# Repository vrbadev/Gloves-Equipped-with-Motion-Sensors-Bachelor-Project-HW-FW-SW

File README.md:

# Gloves Equipped with Motion Sensors (HW & FW & SW)
 This project was created as a part of my bachelor thesis at the Czech Technical University. It contains complete hardware, firmware and software designs for smart Bluetooth gloves equipped with 15 6-DOF IMU sensors.

## About the Bachelor Thesis (Abstract)

This bachelor thesis focuses on the development of gloves equipped with motion sensors. The result of this work is supposed to be a functional device including 3D visualisation of measured bending of all fingers, so hand gestures can be determined. First of all, the theory of Bluetooth Low Energy devices is presented.The next chapter contains an explanation of hardware design details. Then the software implementation for the programmable BLE module is presented. Explanation of the theory of quaternion representation of the rotation and orientation in space for Madgwick's AHRS algorithm can be also found in this work. Python language has been chosen for implementing the visualisation. The thesis is completed with achieved results and ideas for further development.

Full text (in Czech language) is available at: https://dspace.cvut.cz/handle/10467/87657?locale-attribute=en

## Repository Contents

* **Hardware folder** - Contains complete Autodesk EAGLE projects for all related PCBs, including PDF schematics and layout visualisations.
* **Gerber folder** - Contains GERBER production archives for all of the designed PCBs.
* **Firmware folder** - Contains complete Keil uVision project with the firmware for the STMicroelectronics BlueNRG-M2SA Bluetooth module.
* **Software folder** - Contains Python software used for processing of the IMU data and for the visualisation.

## 3D Visualisation Software

A screenshot of the Python visualiser and the static code analysis are shown below.

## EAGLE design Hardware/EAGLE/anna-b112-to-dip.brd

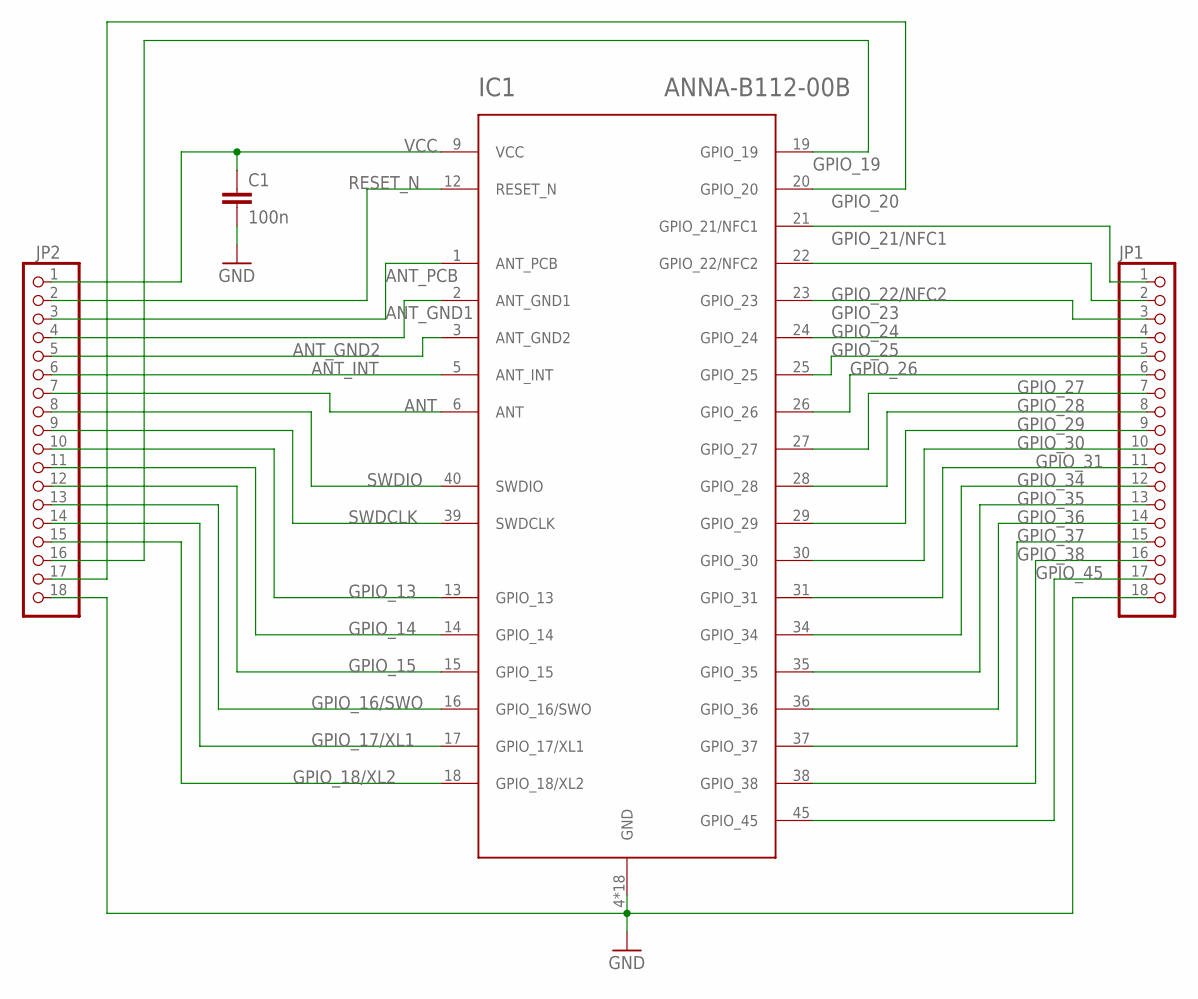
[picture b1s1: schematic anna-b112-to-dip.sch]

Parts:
C1: 100n; C0805
IC1: ANNA-B112-00B; ANNA-B112
JP1, JP2: PINHD-1X18; 1X18

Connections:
ANT: IC1.6 (ANT), JP2.7
ANT_GND1: IC1.2 (ANT_GND1), JP2.4
ANT_GND2: IC1.3 (ANT_GND2), JP2.5
ANT_INT: IC1.5 (ANT_INT), JP2.6
ANT_PCB: IC1.1 (ANT_PCB), JP2.3
GND: C1.2, IC1.4 (GND), IC1.7 (GND), IC1.8 (GND), IC1.10 (GND), IC1.11 (GND), IC1.32 (GND), IC1.33 (GND), IC1.41 (GND), IC1.42 (GND), IC1.43 (GND), IC1.44 (GND), IC1.46 (GND), IC1.47 (GND), IC1.48 (GND), IC1.49 (GND), IC1.50 (GND), IC1.51 (GND), IC1.52 (GND), JP1.18, JP2.18
GPIO_13: IC1.13 (GPIO_13), JP2.10
GPIO_14: IC1.14 (GPIO_14), JP2.11
GPIO_15: IC1.15 (GPIO_15), JP2.12
GPIO_16/SWO: IC1.16 (GPIO_16/SWO), JP2.13
GPIO_17/XL1: IC1.17 (GPIO_17/XL1), JP2.14
GPIO_18/XL2: IC1.18 (GPIO_18/XL2), JP2.15
GPIO_19: IC1.19 (GPIO_19), JP2.16
GPIO_20: IC1.20 (GPIO_20), JP2.17
GPIO_21/NFC1: IC1.21 (GPIO_21/NFC1), JP1.1
GPIO_22/NFC2: IC1.22 (GPIO_22/NFC2), JP1.2
GPIO_23: IC1.23 (GPIO_23), JP1.3
GPIO_24: IC1.24 (GPIO_24), JP1.4
GPIO_25: IC1.25 (GPIO_25), JP1.5
GPIO_26: IC1.26 (GPIO_26), JP1.6
GPIO_27: IC1.27 (GPIO_27), JP1.7
GPIO_28: IC1.28 (GPIO_28), JP1.8
GPIO_29: IC1.29 (GPIO_29), JP1.9
GPIO_30: IC1.30 (GPIO_30), JP1.10
GPIO_31: IC1.31 (GPIO_31), JP1.11
GPIO_34: IC1.34 (GPIO_34), JP1.12
GPIO_35: IC1.35 (GPIO_35), JP1.13
GPIO_36: IC1.36 (GPIO_36), JP1.14
GPIO_37: IC1.37 (GPIO_37), JP1.15
GPIO_38: IC1.38 (GPIO_38), JP1.16
GPIO_45: IC1.45 (GPIO_45), JP1.17
RESET_N: IC1.12 (RESET_N), JP2.2
SWDCLK: IC1.39 (SWDCLK), JP2.9
SWDIO: IC1.40 (SWDIO), JP2.8
VCC: C1.1, IC1.9 (VCC), JP2.1

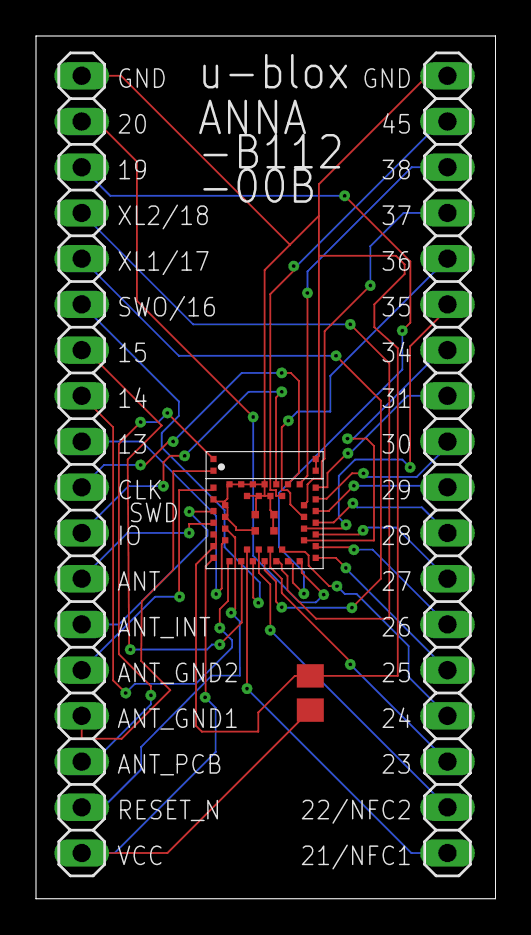
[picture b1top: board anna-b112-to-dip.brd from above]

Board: 2 copper layers, 25.5 x 47.9 mm, 4 parts (0 on the bottom side), 35 nets.

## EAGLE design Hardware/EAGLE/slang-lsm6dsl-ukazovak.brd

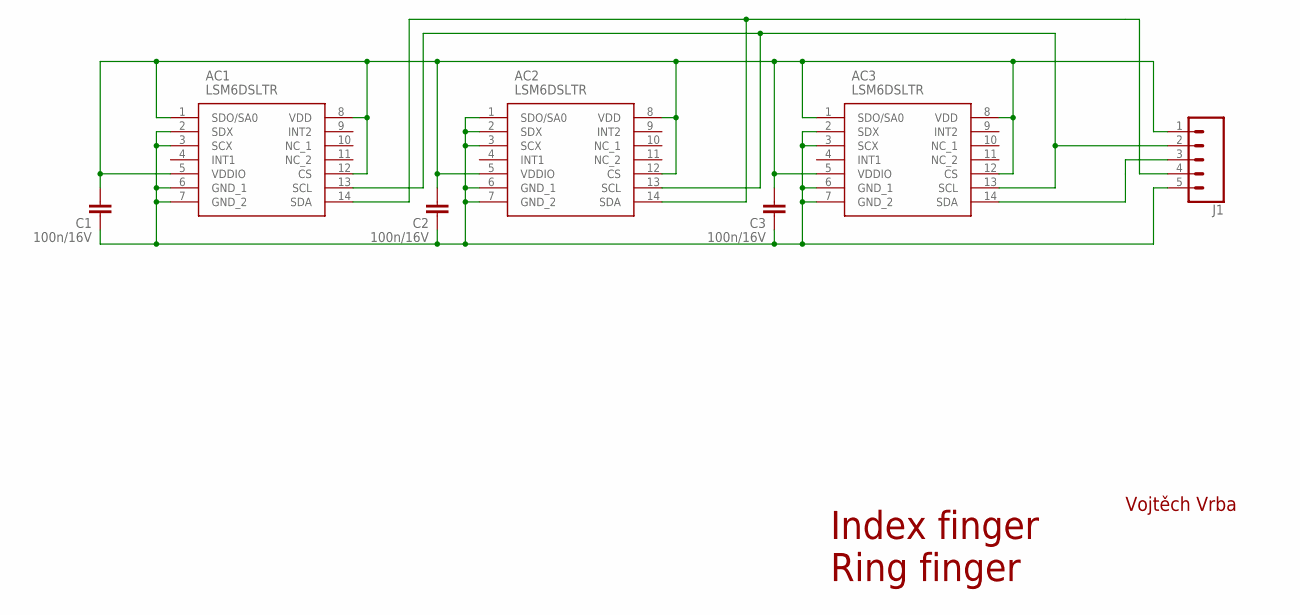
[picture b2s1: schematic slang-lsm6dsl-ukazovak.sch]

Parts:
AC1, AC2, AC3: LSM6DSLTR; LGA-14(2.5X3X0.86)
C1, C2, C3: 100n/16V; C0603
J1: CONN_051.27MM; 1X05_1.27MM

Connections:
GND: AC1.2 (SDX), AC1.3 (SCX), AC1.6 (GND_1), AC1.7 (GND_2), AC2.1 (SDO/SA0), AC2.2 (SDX), AC2.3 (SCX), AC2.6 (GND_1), AC2.7 (GND_2), AC3.2 (SDX), AC3.3 (SCX), AC3.6 (GND_1), AC3.7 (GND_2), C1.1, C2.1, C3.1, J1.5
SCL: AC1.13 (SCL), AC2.13 (SCL), AC3.13 (SCL), J1.2
SDA: AC1.14 (SDA), AC2.14 (SDA), J1.4
SDA2: AC3.14 (SDA), J1.3
VDD: AC1.1 (SDO/SA0), AC1.5 (VDDIO), AC1.8 (VDD), AC1.12 (CS), AC2.5 (VDDIO), AC2.8 (VDD), AC2.12 (CS), AC3.1 (SDO/SA0), AC3.5 (VDDIO), AC3.8 (VDD), AC3.12 (CS), C1.2, C2.2, C3.2, J1.1

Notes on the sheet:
Index finger Ring finger
Vojtěch Vrba

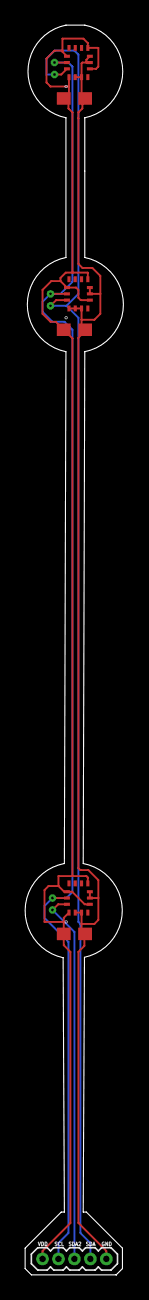
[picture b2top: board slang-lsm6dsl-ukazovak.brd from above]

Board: 2 copper layers, 7.8 x 99.5 mm, 7 parts (0 on the bottom side), 5 nets.

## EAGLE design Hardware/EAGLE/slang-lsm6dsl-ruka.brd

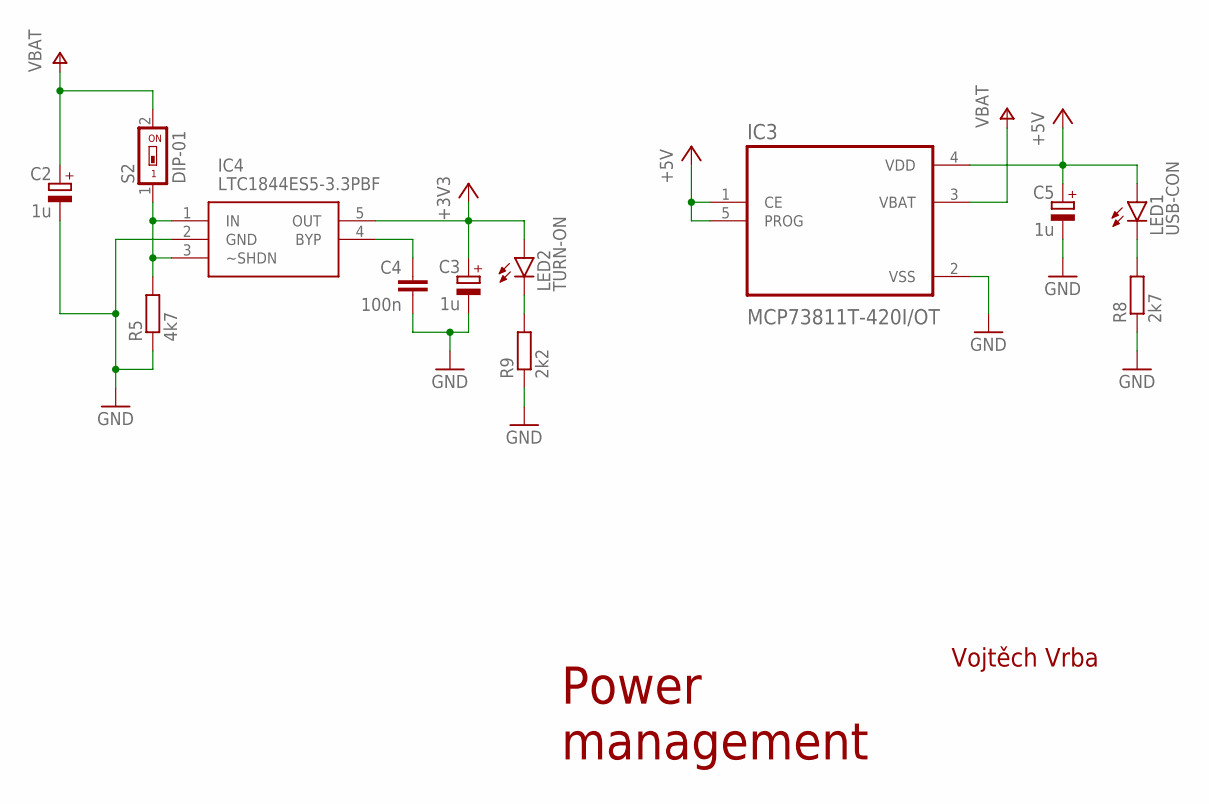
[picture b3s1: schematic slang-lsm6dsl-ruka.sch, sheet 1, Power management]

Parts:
C2, C3, C5: 1u; SMC_A
C4: 100n; C0805
IC3: MCP73811T-420I/OT; SOT95P280X145-5N
IC4: LTC1844ES5-3.3PBF; SOT95P280X100-5N
LED1: USB-CON; CHIP-LED0805
LED2: TURN-ON; CHIP-LED0805
R5: 4k7; R0805
R8: 2k7; R0805
R9: 2k2; R0805
S2: DIP-01; SMS-001

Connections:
+3V3: C3.+, IC4.5 (OUT), LED2.A; also elsewhere on the board
+5V: C5.+, IC3.1 (CE), IC3.4 (VDD), IC3.5 (PROG), LED1.A; also elsewhere on the board
GND: C2.-, C3.-, C4.2, C5.-, IC3.2 (VSS), IC4.2 (GND), R5.1, R8.1, R9.1; also elsewhere on the board
unnamed: LED1.C, R8.2
unnamed: C4.1, IC4.4 (BYP)
unnamed: IC4.1 (IN), IC4.3 (~SHDN), R5.2, S2.1
unnamed: LED2.C, R9.2
V+: C2.+, IC3.3 (VBAT), S2.2; also elsewhere on the board

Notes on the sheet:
Vojtěch Vrba
Power management

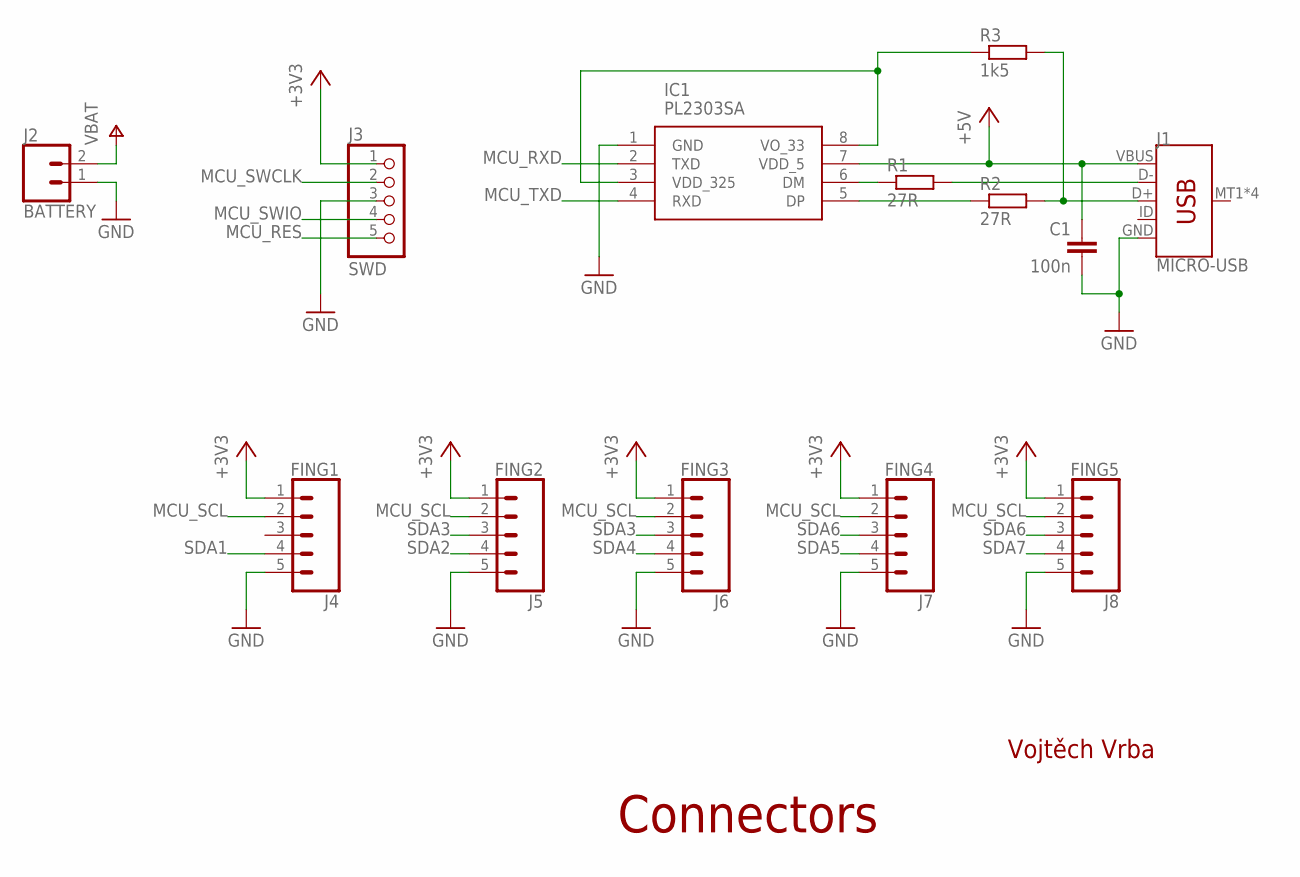
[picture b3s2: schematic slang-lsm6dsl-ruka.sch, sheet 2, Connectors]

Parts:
C1: 100n; C0805
IC1: PL2303SA; SOIC127P600X170-8N
J1: MICRO-USB; USB-MICROB
J2: BATTERY; SCREWTERMINAL-5MM-2
J3: SWD; 1X05/90
J4: FING1; 1X05_1.27MM
J5: FING2; 1X05_1.27MM
J6: FING3; 1X05_1.27MM
J7: FING4; 1X05_1.27MM
J8: FING5; 1X05_1.27MM
R1, R2: 27R; R0805
R3: 1k5; R0805

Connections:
+3V3: J3.1, J4.1, J5.1, J6.1, J7.1, J8.1; also elsewhere on the board
+5V: C1.1, IC1.7 (VDD_5), J1.VBUS; also elsewhere on the board
GND: C1.2, IC1.1 (GND), J1.GND, J2.1, J3.3, J4.5, J5.5, J6.5, J7.5, J8.5; also elsewhere on the board
MCU_RES: J3.5; also elsewhere on the board
MCU_RXD: IC1.2 (TXD); also elsewhere on the board
MCU_SCL: J4.2, J5.2, J6.2, J7.2, J8.2; also elsewhere on the board
MCU_SWCLK: J3.2; also elsewhere on the board
MCU_SWIO: J3.4; also elsewhere on the board
MCU_TXD: IC1.4 (RXD); also elsewhere on the board
unnamed: IC1.6 (DM), R1.1
unnamed: J1.D-, R1.2
unnamed: J1.D+, R2.2, R3.2
unnamed: IC1.5 (DP), R2.1
unnamed: IC1.3 (VDD_325), IC1.8 (VO_33), R3.1
SDA1: J4.4; also elsewhere on the board
SDA2: J5.4; also elsewhere on the board
SDA3: J5.3, J6.3; also elsewhere on the board
SDA4: J6.4; also elsewhere on the board
SDA5: J7.4; also elsewhere on the board
SDA6: J7.3, J8.3; also elsewhere on the board
SDA7: J8.4; also elsewhere on the board
V+: J2.2; also elsewhere on the board

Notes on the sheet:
Connectors
Vojtěch Vrba

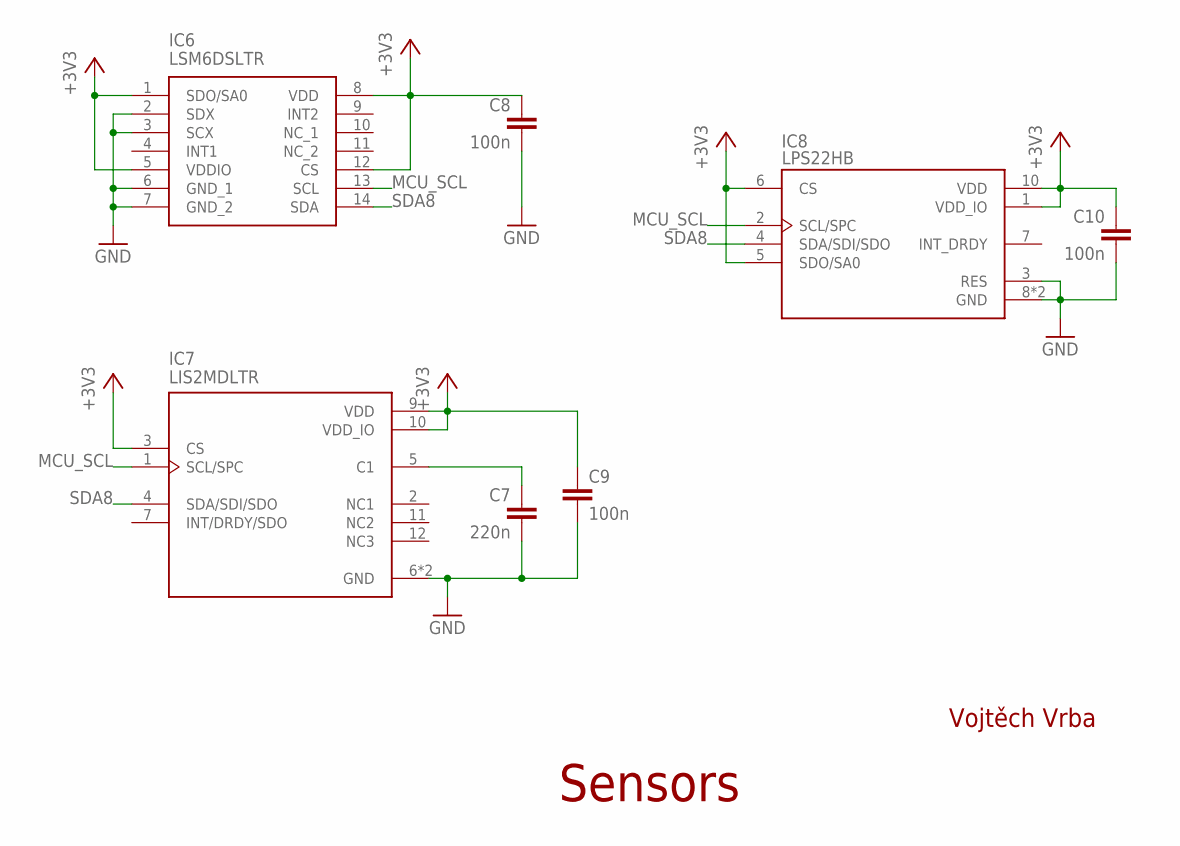
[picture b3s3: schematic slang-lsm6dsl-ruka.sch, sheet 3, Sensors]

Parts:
C7: 220n; C0805
C8, C9, C10: 100n; C0805
IC6: LSM6DSLTR; LGA-14(2.5X3X0.86)
IC7: LIS2MDLTR; PQFN50P200X200X70-12N
IC8: LPS22HB; LGA10R50P2X3_200X200X80

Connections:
+3V3: C8.1, C9.1, C10.1, IC6.1 (SDO/SA0), IC6.5 (VDDIO), IC6.8 (VDD), IC6.12 (CS), IC7.3 (CS), IC7.9 (VDD), IC7.10 (VDD_IO), IC8.1 (VDD_IO), IC8.5 (SDO/SA0), IC8.6 (CS), IC8.10 (VDD); also elsewhere on the board
GND: C7.2, C8.2, C9.2, C10.2, IC6.2 (SDX), IC6.3 (SCX), IC6.6 (GND_1), IC6.7 (GND_2), IC7.6 (GND), IC7.8 (GND), IC8.3 (RES), IC8.8 (GND), IC8.9 (GND); also elsewhere on the board
MCU_SCL: IC6.13 (SCL), IC7.1 (SCL/SPC), IC8.2 (SCL/SPC); also elsewhere on the board
unnamed: C7.1, IC7.5 (C1)
SDA8: IC6.14 (SDA), IC7.4 (SDA/SDI/SDO), IC8.4 (SDA/SDI/SDO); also elsewhere on the board

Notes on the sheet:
Vojtěch Vrba
Sensors

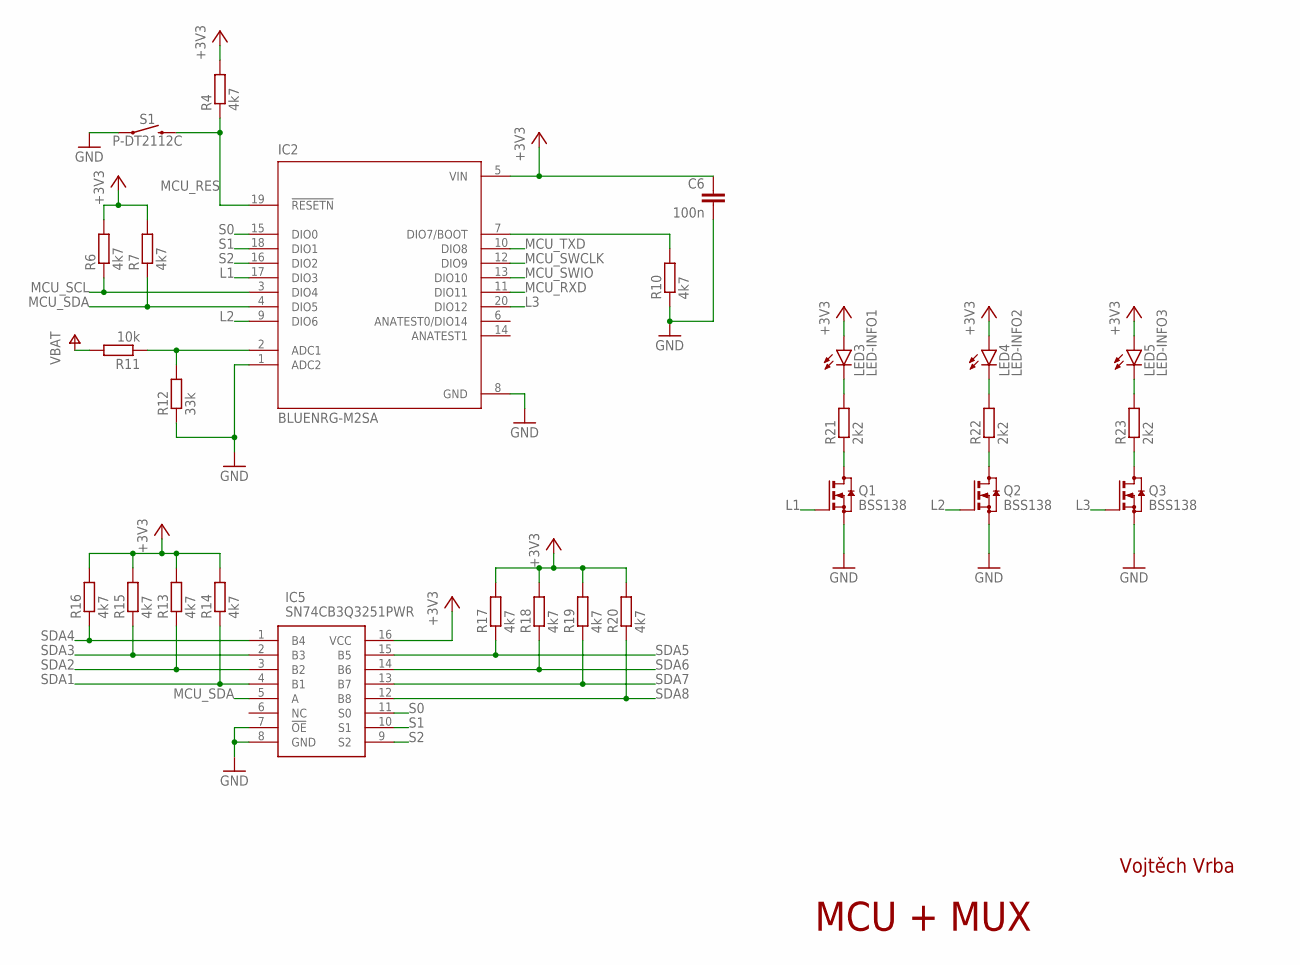
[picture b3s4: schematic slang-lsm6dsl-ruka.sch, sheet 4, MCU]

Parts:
C6: 100n; C0805
IC2: BLUENRG-M2SA; XCVR_BLUENRG-M2SA
IC5: SN74CB3Q3251PWR; SOP65P640X120-16N
LED3: LED-INFO1; CHIP-LED0805
LED4: LED-INFO2; CHIP-LED0805
LED5: LED-INFO3; CHIP-LED0805
Q1, Q2, Q3: BSS138; SOT23
R4, R6, R7, R10, R13, R14, R15, R16, R17, R18, R19, R20: 4k7; R0805
R11: 10k; R0805
R12: 33k; R0805
R21, R22, R23: 2k2; R0805
S1: P-DT2112C; TACTILE_SWITCH_SMD_6.0X3.5MM

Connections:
+3V3: C6.1, IC2.5 (VIN), IC5.16 (VCC), LED3.A, LED4.A, LED5.A, R4.2, R6.2, R7.2, R13.2, R14.2, R15.2, R16.2, R17.2, R18.2, R19.2, R20.2; also elsewhere on the board
GND: C6.2, IC2.1 (ADC2), IC2.8 (GND), IC5.7 (!OE), IC5.8 (GND), Q1.2 (S), Q2.2 (S), Q3.2 (S), R10.1, R12.1, S1.1; also elsewhere on the board
L1: IC2.17 (DIO3), Q1.1 (G)
L2: IC2.9 (DIO6), Q2.1 (G)
L3: IC2.20 (DIO12), Q3.1 (G)
MCU_RES: IC2.19 (!RESETN), R4.1, S1.2; also elsewhere on the board
MCU_RXD: IC2.11 (DIO11); also elsewhere on the board
MCU_SCL: IC2.3 (DIO4), R6.1; also elsewhere on the board
MCU_SDA: IC2.4 (DIO5), IC5.5 (A), R7.1
MCU_SWCLK: IC2.12 (DIO9); also elsewhere on the board
MCU_SWIO: IC2.13 (DIO10); also elsewhere on the board
MCU_TXD: IC2.10 (DIO8); also elsewhere on the board
unnamed: IC2.7 (DIO7/BOOT), R10.2
unnamed: IC2.2 (ADC1), R11.1, R12.2
unnamed: LED3.C, R21.2
unnamed: Q1.3 (D), R21.1
unnamed: LED4.C, R22.2
unnamed: Q2.3 (D), R22.1
unnamed: LED5.C, R23.2
unnamed: Q3.3 (D), R23.1
S0: IC2.15 (DIO0), IC5.11 (S0)
S1: IC2.18 (DIO1), IC5.10 (S1)
S2: IC2.16 (DIO2), IC5.9 (S2)
SDA1: IC5.4 (B1), R14.1; also elsewhere on the board
SDA2: IC5.3 (B2), R13.1; also elsewhere on the board
SDA3: IC5.2 (B3), R15.1; also elsewhere on the board
SDA4: IC5.1 (B4), R16.1; also elsewhere on the board
SDA5: IC5.15 (B5), R17.1; also elsewhere on the board
SDA6: IC5.14 (B6), R18.1; also elsewhere on the board
SDA7: IC5.13 (B7), R19.1; also elsewhere on the board
SDA8: IC5.12 (B8), R20.1; also elsewhere on the board
V+: R11.2; also elsewhere on the board

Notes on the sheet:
Vojtěch Vrba
MCU + MUX

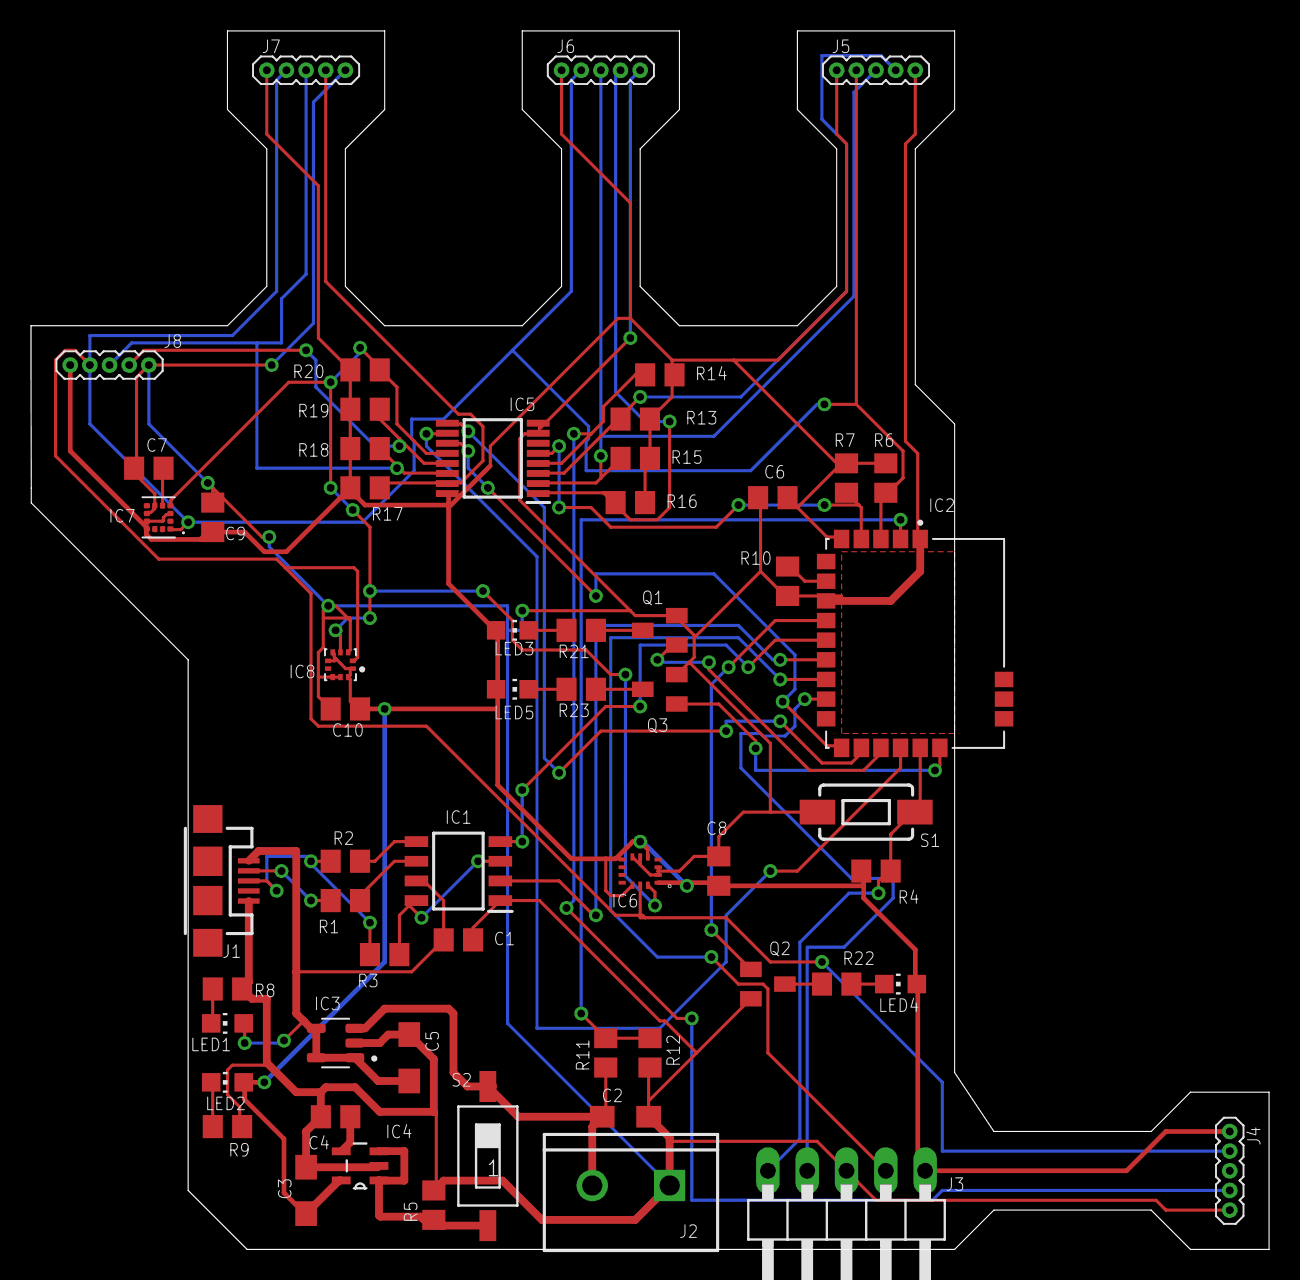
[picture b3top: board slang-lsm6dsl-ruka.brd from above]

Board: 2 copper layers, 80.0 x 78.7 mm, 59 parts (0 on the bottom side), 43 nets.

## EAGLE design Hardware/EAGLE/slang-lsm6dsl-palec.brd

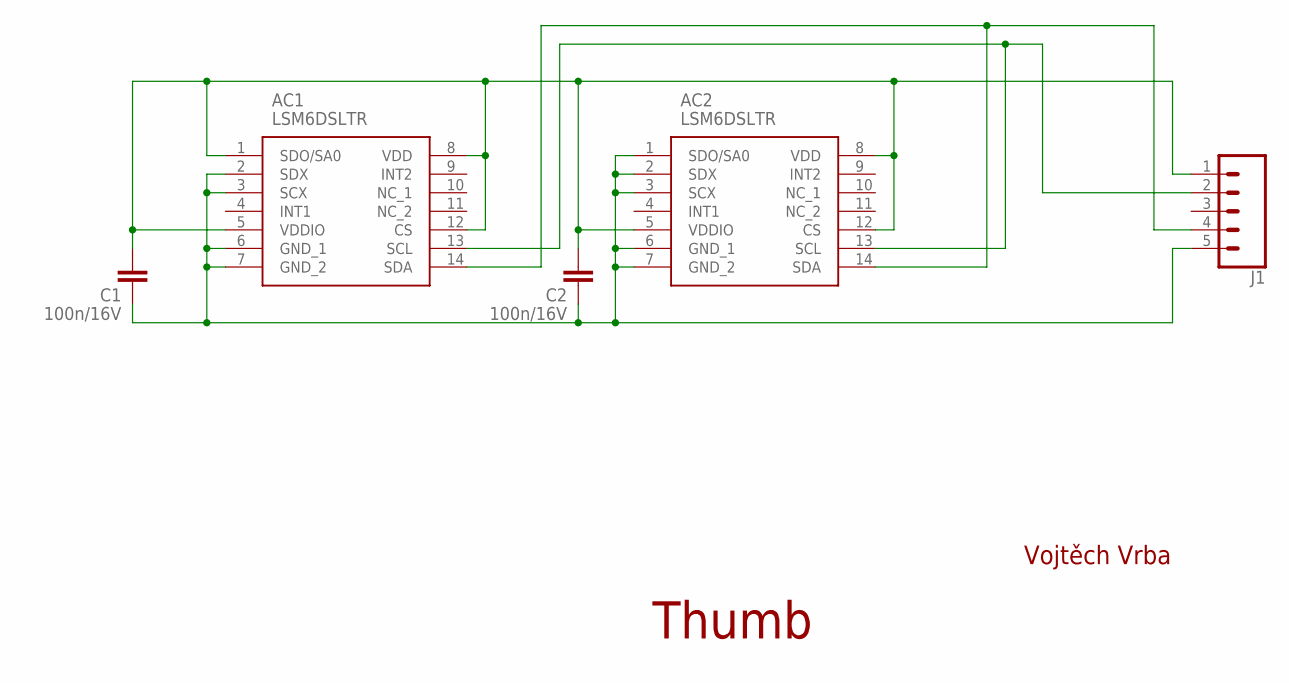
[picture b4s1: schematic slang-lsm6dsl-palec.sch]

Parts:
AC1, AC2: LSM6DSLTR; LGA-14(2.5X3X0.86)
C1, C2: 100n/16V; C0603
J1: CONN_051.27MM; 1X05_1.27MM

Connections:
GND: AC1.2 (SDX), AC1.3 (SCX), AC1.6 (GND_1), AC1.7 (GND_2), AC2.1 (SDO/SA0), AC2.2 (SDX), AC2.3 (SCX), AC2.6 (GND_1), AC2.7 (GND_2), C1.1, C2.1, J1.5
SCL: AC1.13 (SCL), AC2.13 (SCL), J1.2
SDA: AC1.14 (SDA), AC2.14 (SDA), J1.4
VDD: AC1.1 (SDO/SA0), AC1.5 (VDDIO), AC1.8 (VDD), AC1.12 (CS), AC2.5 (VDDIO), AC2.8 (VDD), AC2.12 (CS), C1.2, C2.2, J1.1

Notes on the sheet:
Thumb
Vojtěch Vrba

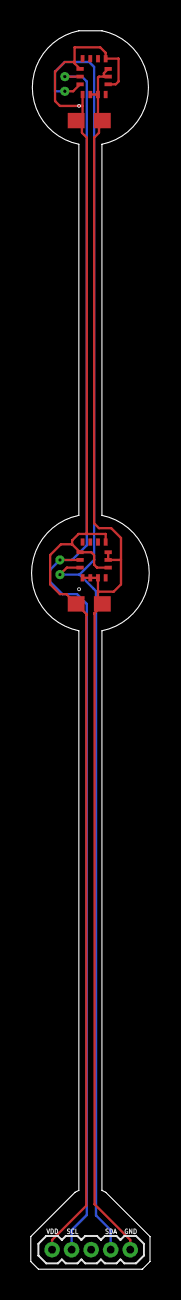
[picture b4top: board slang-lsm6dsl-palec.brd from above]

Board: 2 copper layers, 7.8 x 80.5 mm, 5 parts (0 on the bottom side), 4 nets.

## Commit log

2022-12-30 Initial release

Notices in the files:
parts and their libraries:
SparkFun-Connectors: Licensing: Creative Commons ShareAlike 4.0 International - https://creativecommons.org/licenses/by-sa/4.0
